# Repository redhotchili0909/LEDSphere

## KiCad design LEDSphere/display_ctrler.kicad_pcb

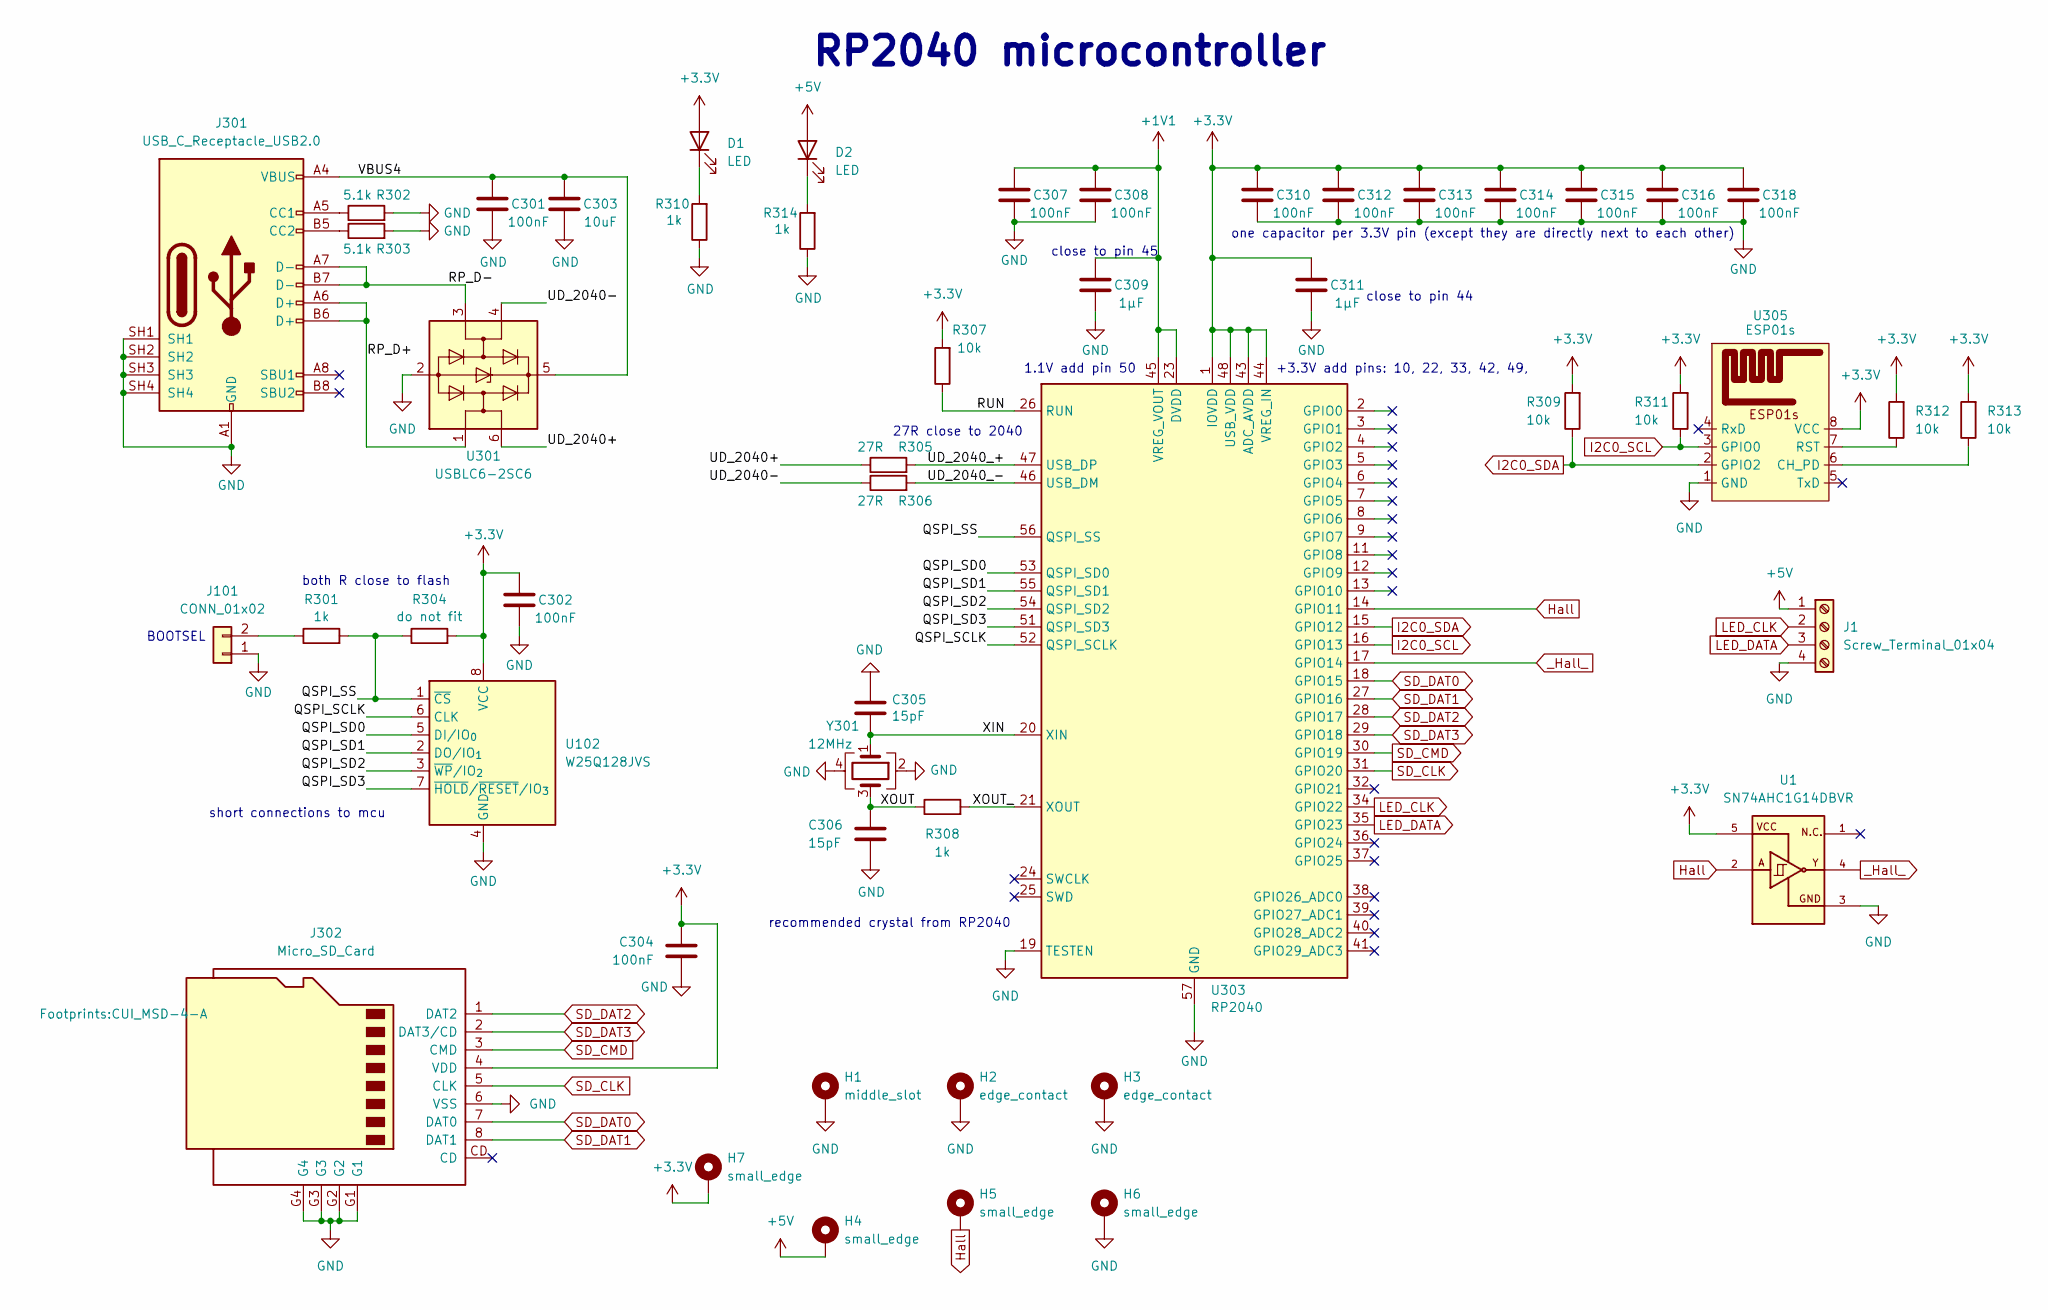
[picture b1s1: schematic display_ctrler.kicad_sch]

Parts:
C301, C302, C304, C310, C312, C313, C314, C315, C316: 100nF; C_0603_1608Metric; LCSC C307331
C303: 10uF; C_1206_3216Metric; LCSC C307331
C305, C306: 15pF; C_0603_1608Metric; LCSC C1557
C307, C308, C318: 100nF; C_0402_1005Metric; LCSC C307331
C309: 1µF; C_0402_1005Metric; LCSC C52923
C311: 1µF; C_0603_1608Metric; LCSC C52923
D1, D2: LED; LED_0805_2012Metric
H1: middle_slot
H2, H3: edge_contact
H4, H5, H6, H7: small_edge; edge_contact_small
J1: Screw_Terminal_01x04; PHOENIX_1727036
J101: CONN_01x02; PinHeader_1x02_P2.54mm_Vertical; MPN 732-5315-ND
J301: USB_C_Receptacle_USB2.0; CUI_UJ20-C-V-C-1-SMT-TR; LCSC C3001289
J302: Micro_SD_Card; CUI_MSD-4-A; LCSC C5155564
R301, R308: 1k; R_0603_1608Metric; LCSC C11702
R302, R303: 5.1k; R_0603_1608Metric; LCSC C25905
R304: do not fit; R_0603_1608Metric
R305, R306: 27R; R_0603_1608Metric; LCSC C321419
R307, R309, R311, R312, R313: 10k; R_0603_1608Metric; LCSC C25744
R310, R314: 1k; R_0603_1608Metric; LCSC C25744
U1: SN74AHC1G14DBVR; SOT-23-5; PARTREV Q
U102: W25Q128JVS; SOIC-8_5.3x5.3mm_P1.27mm
U301: USBLC6-2SC6; SOT-23-6; LCSC C2687116
U303: RP2040; QFN-56-1EP_7x7mm_P0.4mm_EP3.2x3.2mm; LCSC C2040
U305: ESP01s; ESP01s_SMD
Y301: 12MHz; Crystal_SMD_3225-4Pin_3.2x2.5mm; LCSC C9002

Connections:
+1V1: C307.2, C308.2, C309.2, U303.23 (DVDD), U303.45 (VREG_VOUT), U303.50 (DVDD)
+3.3V: C302.2, C304.1, C310.2, C311.2, C312.2, C313.2, C314.2, C315.2, C316.2, C318.2, D1.2 (A), H7.1 (1_1), J302.4 (VDD), R304.2, R307.2, R309.2, R311.2, R312.2, R313.2, U1.5, U102.8 (VCC), U303.1 (IOVDD), U303.10 (IOVDD), U303.22 (IOVDD), U303.33 (IOVDD), U303.42 (IOVDD), U303.43 (ADC_AVDD), U303.44 (VREG_IN), U303.48 (USB_VDD), U303.49 (IOVDD), U305.8 (VCC)
+5V: D2.2 (A), H4.1 (1_1), J1.1
/QSPI_SCLK: U102.6 (CLK), U303.52 (QSPI_SCLK)
/QSPI_SD0: U102.5 (DI/IO_{0}), U303.53 (QSPI_SD0)
/QSPI_SD1: U102.2 (DO/IO_{1}), U303.55 (QSPI_SD1)
/QSPI_SD2: U102.3 (~WP/IO_{2}), U303.54 (QSPI_SD2)
/QSPI_SD3: U102.7 (~HOLD/~RESET/IO_{3}), U303.51 (QSPI_SD3)
/QSPI_SS: R301.2, R304.1, U102.1 (~CS), U303.56 (QSPI_SS)
/RP_D+: J301.A6 (D+), J301.B6 (D+), U301.1 (I/O1)
/RP_D-: J301.A7 (D-), J301.B7 (D-), U301.3 (I/O2)
/RUN: R307.1, U303.26 (RUN)
/UD_2040+: R305.1, U301.6 (I/O1)
/UD_2040-: R306.1, U301.4 (I/O2)
/UD_2040_+: R305.2, U303.47 (USB_DP)
/UD_2040_-: R306.2, U303.46 (USB_DM)
/VBUS4: C301.2, C303.2, J301.A4 (VBUS), J301.A9 (VBUS), J301.B4 (VBUS), J301.B9 (VBUS), U301.5 (VBUS)
/XIN: C305.2, U303.20 (XIN), Y301.1
/XOUT: C306.1, R308.1, Y301.3
/XOUT_: R308.2, U303.21 (XOUT)
GND: C301.1, C302.1, C303.1, C304.2, C305.1, C306.2, C307.1, C308.1, C309.1, C310.1, C311.1, C312.1, C313.1, C314.1, C315.1, C316.1, C318.1, H1.1 (1_1), H2.1 (1_1), H3.1 (1_1), H6.1 (1_1), J1.4, J101.1, J301.A1 (GND), J301.A12 (GND), J301.B1 (GND), J301.B12 (GND), J301.SH1, J301.SH2, J301.SH3, J301.SH4, J302.6 (VSS), J302.G1, J302.G2, J302.G3, J302.G4, R302.2, R303.2, R310.1, R314.1, U1.3, U102.4 (GND), U301.2 (GND), U303.19 (TESTEN), U303.57 (GND), U305.1 (GND), Y301.2, Y301.4
Hall: H5.1 (1_1), U1.2, U303.14 (GPIO11)
I2C0_SCL: R311.1, U303.16 (GPIO13), U305.3 (GPIO0)
I2C0_SDA: R309.1, U303.15 (GPIO12), U305.2 (GPIO2)
LED_CLK: J1.2, U303.34 (GPIO22)
LED_DATA: J1.3, U303.35 (GPIO23)
unnamed: D1.1 (K), R310.2
unnamed: D2.1 (K), R314.2
unnamed: J101.2, R301.1
unnamed: J301.A5 (CC1), R302.1
unnamed: J301.B5 (CC2), R303.1
unnamed: R313.1, U305.6 (CH_PD)
unnamed: R312.1, U305.7 (RST)
SD_CLK: J302.5 (CLK), U303.31 (GPIO20)
SD_CMD: J302.3 (CMD), U303.30 (GPIO19)
SD_DAT0: J302.7 (DAT0), U303.18 (GPIO15)
SD_DAT1: J302.8 (DAT1), U303.27 (GPIO16)
SD_DAT2: J302.1 (DAT2), U303.28 (GPIO17)
SD_DAT3: J302.2 (DAT3/CD), U303.29 (GPIO18)
_Hall_: U1.4, U303.17 (GPIO14)

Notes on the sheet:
short connections to mcu
27R close to 2040
BOOTSEL
+3.3V add pins: 10, 22, 33, 42, 49,
1.1V add pin 50
close to pin 44
RP2040 microcontroller
one capacitor per 3.3V pin (except they are directly next to each other)
both R close to flash
close to pin 45
recommended crystal from RP2040

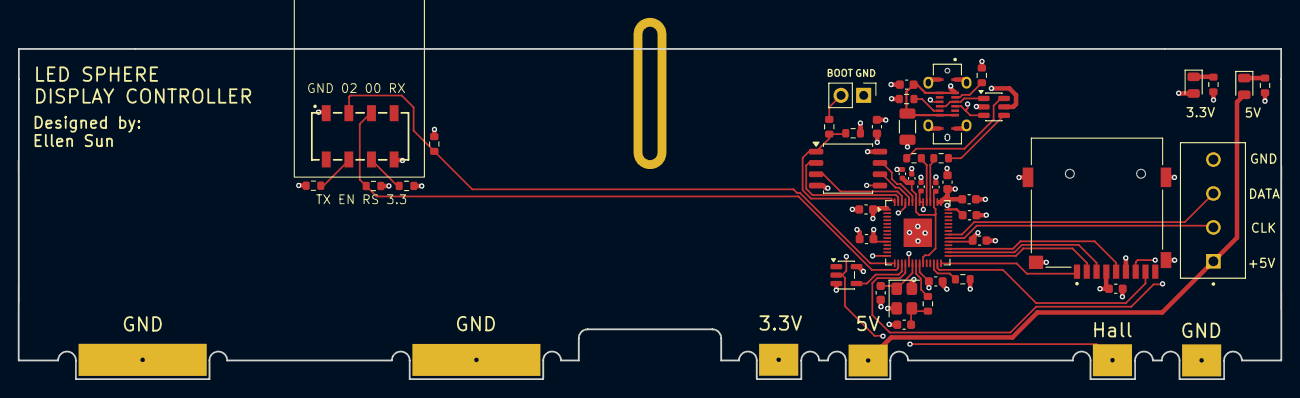
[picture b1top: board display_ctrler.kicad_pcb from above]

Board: 4 copper layers, 141.9 x 37.1 mm, 50 parts (0 on the bottom side), 40 nets.

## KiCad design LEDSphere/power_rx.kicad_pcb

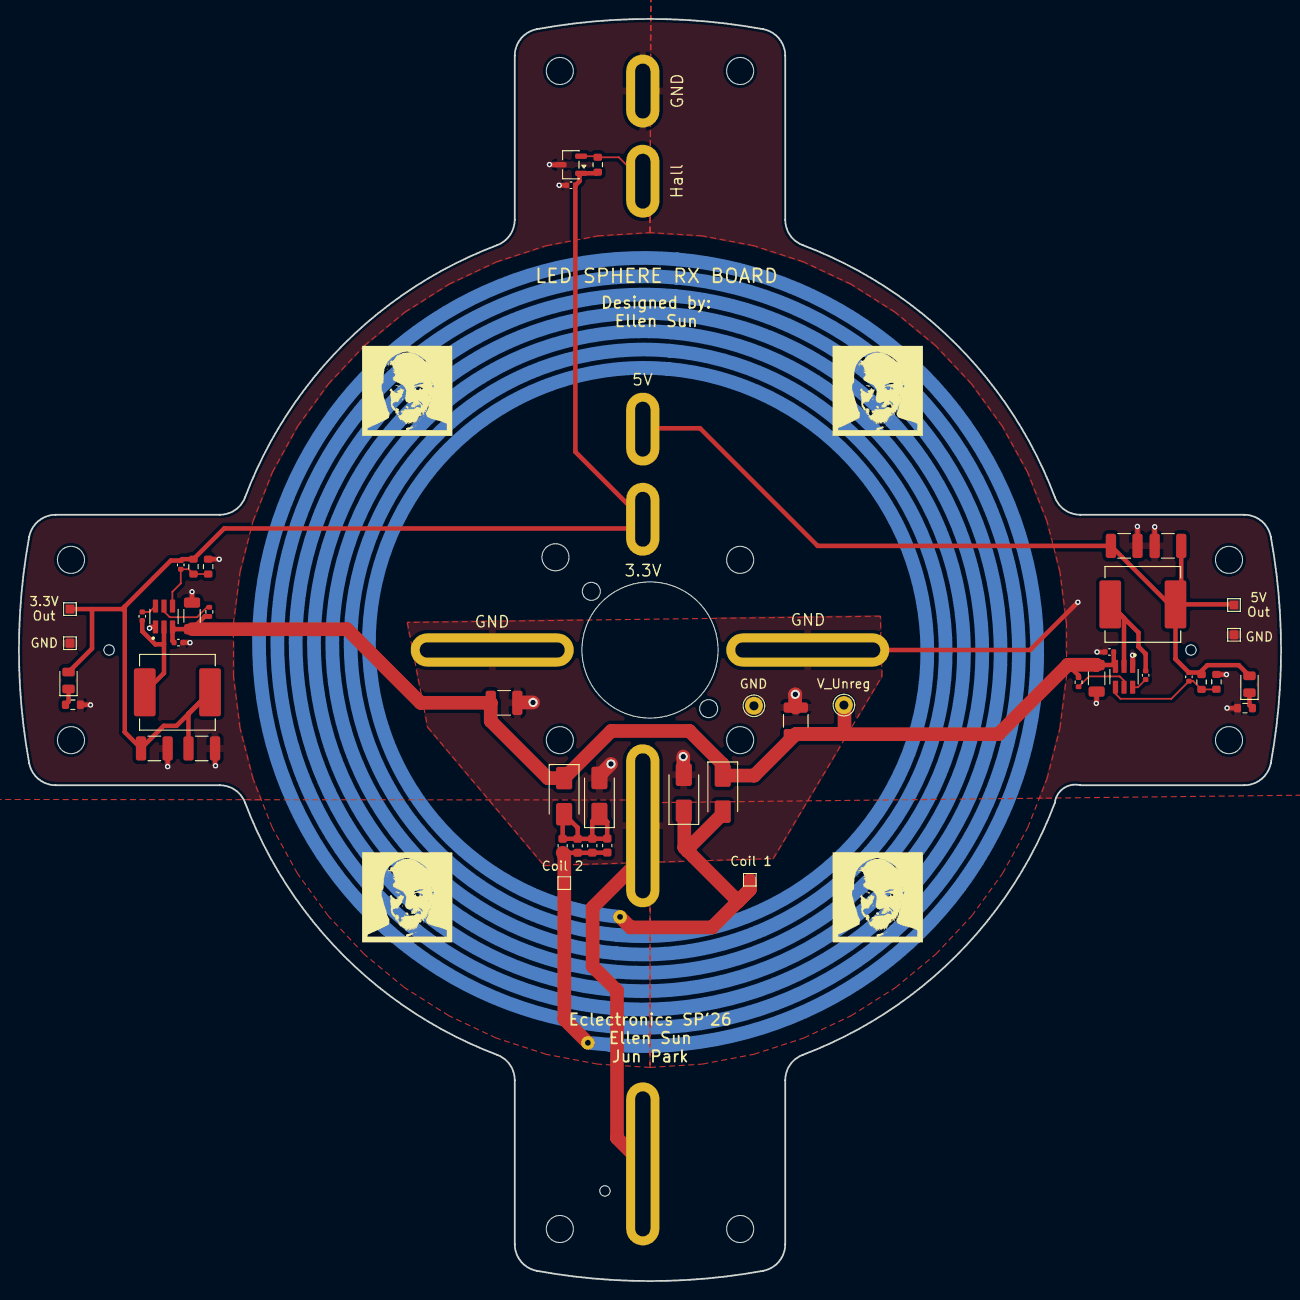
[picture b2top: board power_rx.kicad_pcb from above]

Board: 2 copper layers, 140.0 x 140.0 mm, 55 parts (0 on the bottom side), 18 nets.

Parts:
C1, C2: 10uF; C_1206_3216Metric
C3, C4, C10, C11, C19: 100nF; C_0402_1005Metric
C5, C6, C7, C8: 100nF; C_0603_1608Metric
C9, C12, C13, C14, C15, C16: 22uF; C_1210_3225Metric
C17: 56pF; C_0402_1005Metric
C18: 75pF; C_0402_1005Metric
D1, D2, D3, D4: SS34; D_SMA
D5, D6: LED; LED_0805_2012Metric
L2: 10uH; L_Vishay_IHLP-3232
L3: 15uH; L_Vishay_IHLP-3232
R1, R2: 511k; R_0402_1005Metric
R3, R5: 100k; R_0603_1608Metric
R4: 22.1k; R_0603_1608Metric
R6: 13.3k; R_0603_1608Metric
R7: 10k; R_0603_1608Metric
R8, R9: 1k; R_0603_1608Metric
TP1: Coil2; TestPoint_Pad_1.0x1.0mm
TP2: Coil1; TestPoint_Pad_1.0x1.0mm
TP3: CoilOut; TestPoint_THTPad_D2.0mm_Drill1.0mm
TP4: GND; TestPoint_THTPad_D2.0mm_Drill1.0mm
TP5: 5V; TestPoint_Pad_1.0x1.0mm
TP6: 3.3V; TestPoint_Pad_1.0x1.0mm
TP7, TP8: GND; TestPoint_Pad_1.0x1.0mm
U3, U4: TPS54202HDDCR; SOT95P280X110-6N
U106, U111, U112, U113: slot_long
U107, U108, U109, U110: slot_short
U114: DRV5033FAQDBZR; SOT-23-3

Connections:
+3.3V: C13.2, C15.2, C17.2, C19.1, D5.2 (A), L2.2, R3.2, R7.1, TP6.1 (1_1), U110.1 (1_1), U114.1 (VCC)
+5V: C14.2, C16.2, C18.2, D6.2 (A), L3.2, R5.2, TP5.1 (1_1), U109.1 (1_1)
/U_unreg: C1.2, C2.2, C3.2, C4.2, C9.2, C12.2, D1.1 (K), D3.1 (K), R1.2, R2.2, TP3.1 (1_1), U3.3 (VIN), U4.3 (VIN)
/coil1: D3.2 (A), D4.1 (K), TP2.1 (1_1)
/coil2: C5.1, C6.1, C7.1, C8.1, TP1.1 (1_1)
GND: C1.1, C2.1, C3.1, C4.1, C9.1, C12.1, C13.1, C14.1, C15.1, C16.1, C19.2, D2.2 (A), D4.2 (A), R4.1, R6.1, R8.2, R9.2, TP4.1 (1_1), TP7.1 (1_1), TP8.1 (1_1), U3.1 (GND), U4.1 (GND), U106.1 (1_1), U107.1 (1_1), U111.1 (1_1), U112.1 (1_1), U113.1 (1_1), U114.3 (GND)
Hall: R7.2, U108.1 (1_1), U114.2 (OUT)
unnamed: C5.2, C6.2, C7.2, C8.2, D1.2 (A), D2.1 (K)
unnamed: D5.1 (K), R8.1
unnamed: D6.1 (K), R9.1
unnamed: C10.2, U3.6 (BOOT)
unnamed: R1.1, U3.5 (EN)
unnamed: C17.1, R3.1, R4.2, U3.4 (FB)
unnamed: C10.1, L2.1, U3.2 (SW)
unnamed: C11.2, U4.6 (BOOT)
unnamed: R2.1, U4.5 (EN)
unnamed: C18.1, R5.1, R6.2, U4.4 (FB)
unnamed: C11.1, L3.1, U4.2 (SW)

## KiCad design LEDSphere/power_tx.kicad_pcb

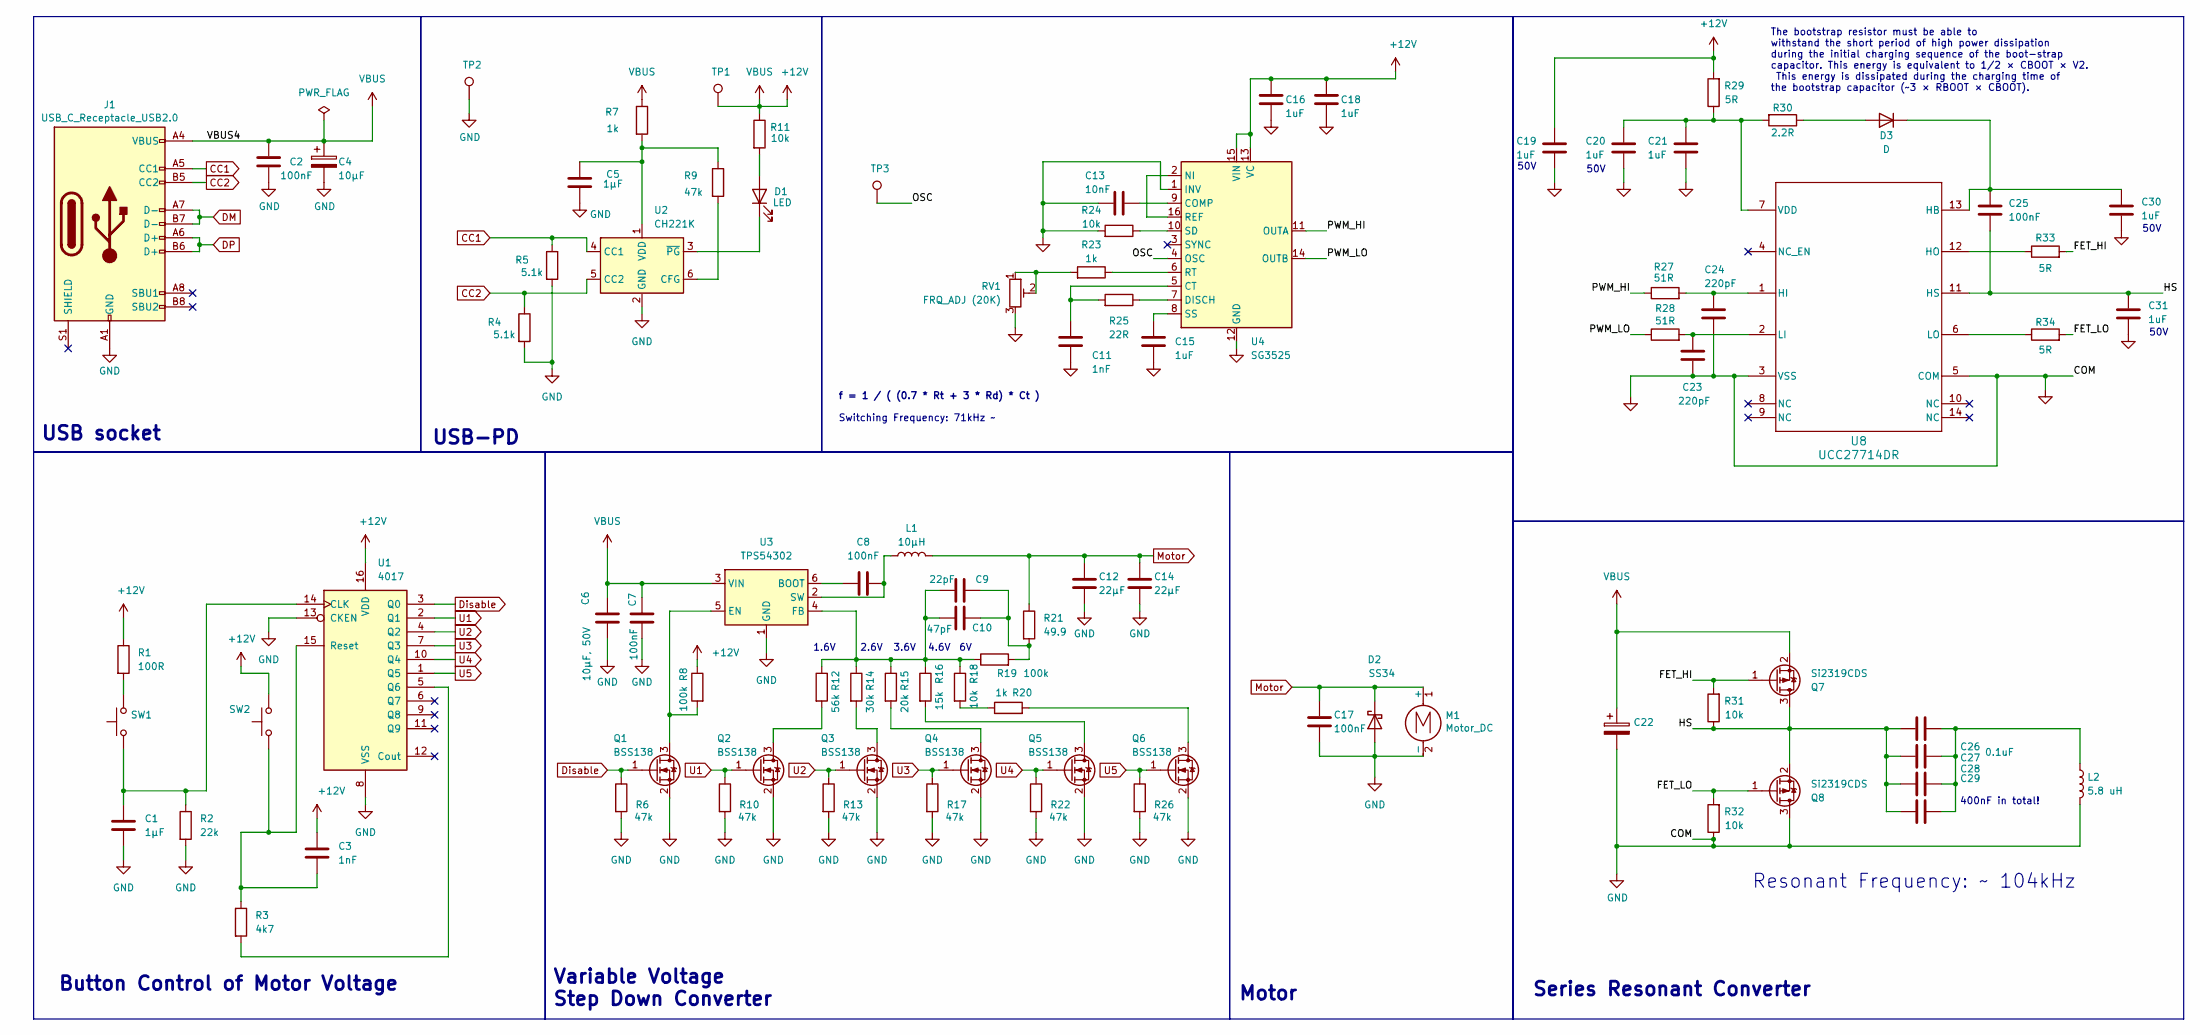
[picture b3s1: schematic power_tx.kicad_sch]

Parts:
C1, C5: 1µF; C_0603_1608Metric; LCSC C15849
C2: 100nF; C_0402_1005Metric; LCSC C307331
C3: 1nF; C_0402_1005Metric; LCSC C1523
C4: 10µF; C_0805_2012Metric; LCSC C440198
C6: 10µF, 50V; C_1206_3216Metric; LCSC C13585
C7, C8, C17, C27: 100nF; C_0603_1608Metric; LCSC C14663
C9: 22pF; C_0603_1608Metric; LCSC C1653
C10: 47pF; C_0603_1608Metric; LCSC C1671
C11: 1nF; C_0603_1608Metric
C12, C14: 22µF; C_1210_3225Metric; LCSC C45783
C13: 10nF; C_0603_1608Metric
C15: 1uF; C_0402_1005Metric
C16, C18, C20, C30, C31: 1uF; C_0805_2012Metric
C19: 1uF; C_1206_3216Metric
C21: 1uF; C_0603_1608Metric
C22: 10µ, 50V; C_1206_3216Metric; LCSC C13585
C23, C24: 220pF; C_0402_1005Metric
C25: 100nF; C_0603_1608Metric
C26: 0.1uF; C_0603_1608Metric; LCSC C14663
C28, C29: 68nF; C_0603_1608Metric; LCSC C14663
D1: LED; LED_0805_2012Metric; LCSC LSM0805412V
D2: SS34; D_SMA; LCSC C8678
D3: D; D_SMA
J1: USB_C_Receptacle_USB2.0; USB_C_Receptacle_GCT_USB4105-xx-A_16P_TopMnt_Horizontal; LCSC C709357
L1: 10µH; L_Vishay_IHLP-3232
L2: 5.8 uH; power_coil
M1: Motor_DC; motor
Q1: BSS138; SOT-23
Q2, Q3, Q4, Q5, Q6: BSS138; SOT-23; LCSC C7420339
Q7, Q8: Si2319CDS; SOT-23
R1: 100R; R_0402_1005Metric; LCSC C25076
R2: 22k; R_0402_1005Metric; LCSC C25768
R3: 4k7; R_0402_1005Metric; LCSC C25900
R4, R5: 5.1k; R_0402_1005Metric; LCSC C25744
R6, R10, R13, R17, R22, R26: 47k; R_0402_1005Metric; LCSC C25792
R7, R20: 1k; R_0402_1005Metric; LCSC C11702
R8, R19: 100k; R_0402_1005Metric; LCSC C25741
R9: 47k; R_0402_1005Metric; LCSC C25744
R11: 10k; R_0603_1608Metric; LCSC C21190
R12: 56k; R_0603_1608Metric; LCSC C23206
R14: 30k; R_0603_1608Metric; LCSC C22984
R15: 20k; R_0402_1005Metric; LCSC C25765
R16: 15k; R_0402_1005Metric; LCSC C25756
R18: 10k; R_0402_1005Metric; LCSC C25744
R21: 49.9; R_0402_1005Metric; LCSC C25120
R23: 1k; R_0402_1005Metric
R24: 10k; R_0402_1005Metric
R25: 22R; R_0402_1005Metric
R27, R28: 51R; R_0603_1608Metric
R29, R33, R34: 5R; R_0603_1608Metric
R30: 2.2R; R_0603_1608Metric
R31, R32: 10k; R_0603_1608Metric
RV1: FRQ_ADJ (20K); TRIM_3362P-1-203LF
SW1, SW2: SW_Push; SW_Tactile_SPST_Angled_PTS645Vx58-2LFS; Part # PTS645VK58-2 LFS
TP1, TP2, TP3: TestPoint; TestPoint_Loop_D1.80mm_Drill1.0mm_Beaded
U1: 4017; STC_SOP-16_3.9x9.9mm_P1.27mm; Part # CD4017BM96
U2: CH221K; SOT-23-6
U3: TPS54302; SOT-23-6; LCSC C311983
U4: SG3525; SO-16N_STM
U8: UCC27714DR; SOIC127P600X175-14N

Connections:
+12V: C2.2, C3.1, C4.1, C6.1, C7.1, C16.1, C18.1, C19.1, C22.1, J1.A4 (VBUS), J1.A9 (VBUS), J1.B4 (VBUS), J1.B9 (VBUS), Q7.2 (S), R1.1, R7.1, R8.1, R11.1, R29.2, SW2.2, TP1.1 (1_1), U1.16 (VDD), U3.3 (VIN), U4.13 (VC), U4.15 (VIN)
/FET_HI: Q7.1 (G), R31.2, R33.2
/FET_LO: Q8.1 (G), R32.2, R34.2
/HS: C25.2, C26.1, C27.1, C28.1, C29.1, C31.1, Q7.3 (D), Q8.2 (S), R31.1, U8.11 (HS)
/OSC: TP3.1 (1_1), U4.4 (OSC)
/PWM_HI: R27.1, U4.11 (OUTA)
/PWM_LO: R28.1, U4.14 (OUTB)
CC1: J1.A5 (CC1), R5.1, U2.4 (CC1)
CC2: J1.B5 (CC2), R4.1, U2.5 (CC2)
DM: J1.A7 (D-), J1.B7 (D-)
DP: J1.A6 (D+), J1.B6 (D+)
Disable: Q1.1 (G), R6.1, U1.3 (Q0)
GND: C1.2, C2.1, C4.2, C5.2, C6.2, C7.2, C11.2, C12.2, C13.1, C14.2, C15.2, C16.2, C17.2, C18.2, C19.2, C20.2, C21.2, C22.2, C23.2, C24.2, C30.2, C31.2, D2.2 (A), J1.A1 (GND), J1.A12 (GND), J1.B1 (GND), J1.B12 (GND), L2.2, M1.2 (-), Q1.2 (S), Q2.2 (S), Q3.2 (S), Q4.2 (S), Q5.2 (S), Q6.2 (S), Q8.3 (D), R2.2, R4.2, R5.2, R6.2, R10.2, R13.2, R17.2, R22.2, R24.2, R26.2, R32.1, RV1.3, TP2.1 (1_1), U1.8 (VSS), U1.13 (CKEN), U2.2 (GND), U3.1 (GND), U4.1 (INV), U4.12 (GND), U8.3 (VSS), U8.5 (COM); also elsewhere on the board
Motor: C12.1, C14.1, C17.1, D2.1 (K), L1.2, M1.1 (+), R21.1
unnamed: C9.2, C10.2, R19.2, R21.2
unnamed 15: C26.2, C27.2, C28.2, C29.2, L2.1; also elsewhere on the board
unnamed: D1.2 (A), R11.2
unnamed: D1.1 (K), U2.3 (~PG)
unnamed: D3.2 (A), R30.1
unnamed: C25.1, C30.1, D3.1 (K), U8.13 (HB)
unnamed: Q1.3 (D), R8.2, U3.5 (EN)
unnamed: Q2.3 (D), R12.2
unnamed: Q3.3 (D), R14.2
unnamed: Q4.3 (D), R15.2
unnamed: Q5.3 (D), R16.2
unnamed: Q6.3 (D), R20.2
unnamed: R1.2, SW1.2
unnamed: R18.2, R20.1
unnamed: R23.2, RV1.1, RV1.2
unnamed: C1.1, R2.1, SW1.1, U1.14 (CLK)
unnamed: R3.2, U1.5 (Q6)
unnamed: C3.2, R3.1, SW2.1, U1.15 (Reset)
unnamed: R9.2, U2.6 (CFG)
unnamed: C5.1, R7.2, R9.1, U2.1 (VDD)
unnamed: C8.1, U3.6 (BOOT)
unnamed: C9.1, C10.1, R12.1, R14.1, R15.1, R16.1, R18.1, R19.1, U3.4 (FB)
unnamed: C8.2, L1.1, U3.2 (SW)
unnamed: C13.2, U4.9 (COMP)
unnamed: C11.1, R25.2, U4.5 (CT)
unnamed: R25.1, U4.7 (DISCH)
unnamed: U4.2 (NI), U4.16 (REF)
unnamed: R23.1, U4.6 (RT)
unnamed: R24.1, U4.10 (SD)
unnamed: C15.1, U4.8 (SS)
unnamed: C24.1, R27.2, U8.1 (HI)
unnamed: R33.1, U8.12 (HO)
unnamed: C23.1, R28.2, U8.2 (LI)
unnamed: R34.1, U8.6 (LO)
unnamed: C20.1, C21.1, R29.1, R30.2, U8.7 (VDD)
U1: Q2.1 (G), R10.1, U1.2 (Q1)
U2: Q3.1 (G), R13.1, U1.4 (Q2)
U3: Q4.1 (G), R17.1, U1.7 (Q3)
U4: Q5.1 (G), R22.1, U1.10 (Q4)
U5: Q6.1 (G), R26.1, U1.1 (Q5)

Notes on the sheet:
Button Control of Motor Voltage
50V
f = 1 / ( (0.7 * Rt + 3 * Rd) * Ct )
2.6V
Variable Voltage Step Down Converter
Series Resonant Converter
Motor
Resonant Frequency: ~ 104kHz
3.6V
USB-PD
1.6V
Switching Frequency: 71kHz ~
4.6V
400nF in total!
USB socket
The bootstrap resistor must be able to withstand the short period of high power dissipation during the initial charging sequence of the boot-strap capacitor. This energy is equivalent to 1/2 × CBOOT × V2. This energy is dissipated during the charging time of the bootstrap capacitor (~3 × RBOOT × CB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

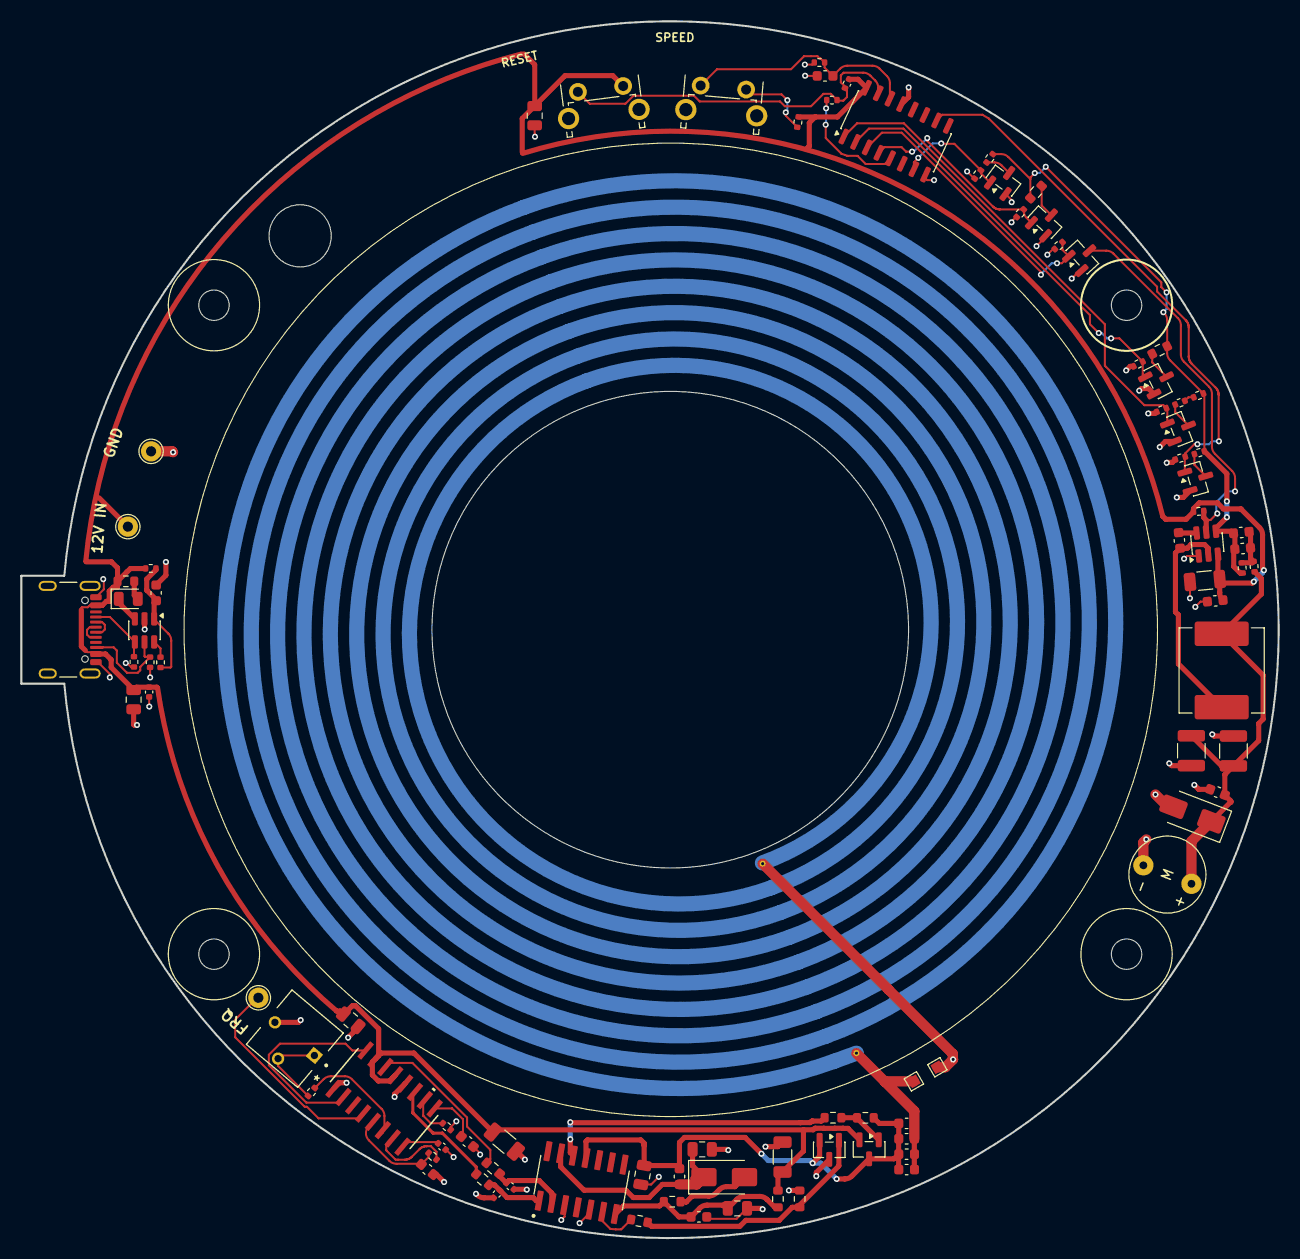
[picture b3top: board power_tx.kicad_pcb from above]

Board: 2 copper layers, 124.0 x 120.0 mm, 93 parts (1 on the bottom side), 54 nets.

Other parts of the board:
TP4, TP5: TestPoint; TestPoint_Pad_1.0x1.0mm

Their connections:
GND: TP5.1 (1_1); also elsewhere on the board
unnamed 15: TP4.1 (1_1); also elsewhere on the board

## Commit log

2026-03-24 Add Initial Power Board Transmitter Design
2026-03-25 started routing drivers, power mosfets
2026-03-25 finished usb-c power delivery aspect - started pwm generator sch
2026-03-26 display controller sch
2026-03-26 finish schm
2026-03-26 create receiver board proj
2026-03-26 first draft of power board
2026-03-26 edit power mosfet orientation
2026-03-26 renamed rx_board project to power_rx
2026-03-26 Add Power Transmitter Footprints
2026-03-26 Add Initial Schematic for Review
2026-03-26 start power rx
2026-03-27 buck
2026-03-27 hall effect sensor
2026-03-30 Add PCB Coil for Transmitter
2026-03-31 Starting Layout
2026-03-31 Start Layout
2026-03-31 Initial Layout (Rounded Tracks)
2026-03-31 Excluded Ground Pour
2026-04-02 start disp pcb layout
2026-04-02 Arrange file structure
2026-04-02 Remove power_rx directory
2026-04-02 finish display controller layout
2026-04-03 display controller add led terminal
2026-04-03 adjust positions
2026-04-03 Modify RX Schm. + Adjusted TX Coil
2026-04-03 Updated Resonance FRQ + Test Points Added
2026-04-05 move edge connections to correct area
2026-04-05 first draft rx power layout
2026-04-05 Most Recent TX Board Changes
2026-04-05 Minor Layout Changes for TX Board
2026-04-07 change footprints
2026-04-07 Altered Button Part
2026-04-07 power rx layout change
2026-04-08 change hall effect sensor
2026-04-08 add in esp10s receptable
2026-04-08 Edit 22uF Footprint to 1210
2026-04-08 wrap up rx
2026-04-09 change things around
2026-04-09 cut gnd plane
2026-04-09 Edit testpoint footprint
2026-04-09 change power rx gnding, add step files of all boards
2026-04-09 Most up to date TX
2026-04-09 adjust test point
2026-04-09 update rx model
2026-04-09 update models
2026-04-11 alter rx to avoid flux lines
2026-04-11 display ctrler changes
2026-04-11 move led terminal up
2026-04-13 add leds
2026-04-13 FINAL PUSHES
2026-04-28 Adding Scope Data
2026-04-28 Add Coil Data
